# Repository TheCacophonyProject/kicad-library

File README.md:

# kicad-library
Cacophony kicad library of 3D models, footprints, and symbols.

## Adding Libraries to Project
- Clone/download git repo.
- Add new environment variable:
    - `Preferences` -> `Configure Paths...`
    - Add new variable with Name=`CAC_KICAD_LIBRARY` and Path=`<path to git repo>`
- Add Symbol library:
    - `Preferences` -> `Manage Symbol Libraries...`
    - Add to Global or Project depending on what you want.
    - Add new library with nickname=`cacophony-library` Path=`${CAC_KICAD_LIBRARY}/cacophony-library.kicad_sym`

- Add Footprint library:
    - `Preferences` -> `Manage Footprint Libraries...`
    - Add to Global or Project depending on what you want.
    - Add new library with nickname=`cacophony-library` Path=`${CAC_KICAD_LIBRARY}/cacophony-library.pretty`

## Adding new parts with eadyeda2kicad
- Install easyeda2kicad https://github.com/uPesy/easyeda2kicad.py
- `cd <path to kicad-library>`
- `easyeda2kicad --full --output ./cacophony-library --lcsc_id <id>`
- To make the footprint link to the 3D model you will need to add `${CAC_KICAD_LIBRARY}` to the start of the 3D model path in the footprint.

## Adding a module to your project
These kicad modules are parts that I have used multiple times in different projects. They contain the schematics and the layout of the footprints.

- With your kicad project open, open the module in a different kicad instance.
-

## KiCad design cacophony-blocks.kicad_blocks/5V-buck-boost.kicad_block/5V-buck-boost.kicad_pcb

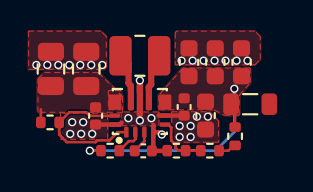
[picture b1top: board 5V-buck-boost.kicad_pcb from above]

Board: 4 copper layers, 17 parts (0 on the bottom side), 10 nets.

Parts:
C1, C2: 22uF; C_0805_2012Metric
C3: 2.2uF; C_0402_1005Metric
C4: 100nF; C_0402_1005Metric
C5: 10uF; C_0402_1005Metric
C6, C7, C8, C9: 22uF; C_0603_1608Metric
FB1: FerriteBead; L_0805_2012Metric
L1: 1.5uH; L_1008_2520Metric
R1, R4: 100k; R_0402_1005Metric
R2: 470k; R_0402_1005Metric
R3: 68k; R_0402_1005Metric
R5: 10k; R_0402_1005Metric
U1: TPS63070

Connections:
5V_EN: R5.2, U1.1 (PS/SYNC), U1.14 (EN)
/5V_L1: L1.1, U1.11 (L1)
/5V_L2: L1.2, U1.9 (L2)
/5V_PG: R4.2, U1.2 (PG)
/5V_PHY: C5.1, C6.1, C7.1, C8.1, C9.1, FB1.1, R2.1, R4.1, U1.7,8 (Vout)
GND: C1.2, C2.2, C3.2, C4.2, C5.2, C6.2, C7.2, C8.2, C9.2, R1.2, U1.4 (GND), U1.6 (FB2), U1.10 (PGND), U1.15 (Vsel)
unnamed: R2.2, R3.2
unnamed: R1.1, R3.1, U1.5 (FB)
unnamed: C4.1, U1.3 (Vaux)
VCC: C1.1, C2.1, C3.1, R5.1, U1.12,13 (Vin)

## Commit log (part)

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2023-05-02 Adding more components
2023-05-10 Added more parts
2024-07-19 Update library
2025-03-07 Add latest parts
2025-12-02 Add more parts
2026-06-26 Update models
2026-06-26 Update library for spool
2026-06-30 update library for battery tester
2026-06-30 Add more components for battery tester
